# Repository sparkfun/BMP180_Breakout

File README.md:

**NOTE:** *This product has been retired from our catalog. If you are looking for more up-to-date info, please check out some of these resources to see how other users are still hacking and improving on this product.*
* *[SparkFun Forum](https://forum.sparkfun.com/)*
* *[Comments Here on GitHub](https://github.com/sparkfun/BMP180_Breakout_Arduino_Library/issues)*
* *[IRC Channel](https://www.sparkfun.com/news/263)*

BMP180_Breakout
===============

Breakout board and example code for the Bosch BMP180 barometric pressure sensor.

Product page: [www.sparkfun.com/products/11824](https://www.sparkfun.com/products/11824)

Datasheet: [github.com/sparkfun/BMP180_Breakout/blob/master/BMP180 Datasheet V2.5.pdf](https://github.com/sparkfun/BMP180_Breakout/blob/master/BMP180%20Datasheet%20V2.5.pdf?raw=true)

Github repository: [github.com/sparkfun/BMP180_Breakout](https://github.com/sparkfun/BMP180_Breakout)

Arduino library installation:
-------------------

This archive contains an Arduino library and example sketch showing how to use this sensor. The library must be installed onto your computer in order for the example code to work correctly.

If you haven't, install the free Arduino IDE (Integrated Development Environment), available at [www.arduino.cc](http://www.arduino.cc). This code was written using Arduino version 1.0.5. and updated to be used with the Arduino library manager of version 1.6.3.

To install without the manager, download the Arduino folder then use the Arduino IDE to add it.  From the IDE, go Sketch->Include Library->"Add .ZIP Library", then choose the Arduino folder that was downloaded.  The IDE will pick proper names from the library.properties file and put the libraries in your user sketch folder.

Teensy library installation:
-------------------

[A. Faruk](https://github.com/unalfaruk) was kind enough to create a version of this library for the [Teensy](https://www.pjrc.com/teensy/) microcontroller family. You can find information on installation and use of this library at: https://github.com/sparkfun/BMP180_Breakout/tree/master/Libraries/Teensy

Running the example sketch:
-------------------

<ol start=1>
<li>Connect the BMP180 breakout board to your Arduino. You can solder wires, use jumper wires and headers, etc.
<p>
"-" (GND) to GND
<br>
"+" (VDD) to 3.3V
<p>
(WARNING: do not connect "+" to 5V or the sensor will be damaged!)
<p>
You will also need to connect the I2C pins (SCL and SDA) to your Arduino.
These pins are different on different Arduino models:
<p>
<table>
<tr>
<td>Any Arduino</td>
<td>SDA&nbsp;</td>
<td>SCL</td>
</tr>
<tr>
<td>Uno, Redboard, Pro/Mini&nbsp;</td>
<td>A4</td>
<td>A5</td>
</tr>
<tr>
<td>Mega2560, Due</td>
<td>20</td>
<td>21</td>
</tr>
<tr>
<td>Leonardo, Pro/Micro</td>
<td>2</td>
<td>3</td>
</tr>
</table>
<p>
Leave the IO (VDDIO) pin unconnected. This pin is for connecting
the BMP180 to systems with lower logic levels such as 1.8V.
</li>
<li>
Connect your Arduino to your computer.
<p>
</li>
<li>
Start the Arduino IDE. Select the proper COM port and board type.
<p>
</li>
<li>
In the Arduino IDE, go to the File menu, and down to Examples/SFE_BMP180/SFE_BMP180_example. If you do not see this item, you likely did not install the library properly. See above.
<p>
</li>
<li>
Upload the sketch to your Arduino.
<p>
</li>
<li>
Open the Serial Monitor window (magnifying glass icon un upper right of IDE).
<p>
</li>
<li>
Set the Serial Monitor to 9600 baud (menu in bottom right).
<p>
</li>
</ol>
You should now be seeing pressure measurements in the Serial Monitor window. If you see errors, you may not have connected the BMP180 Breakout Board to your Arduino properly. See step 1 above.

If you have questions, don't hesistate to contact us at techsupport@sparkfun.com.

Have fun!
Your friends at SparkFun.

License Informatiom
-------------------

Software and hardware license information can be found at: https://github.com/sparkfun/BMP180_Breakout/blob/master/LICENSE.md

Authors
-------

 * Mike Grusin, SparkFun Electronics

Acknowledgements
----------------

 * The SFE_BMP180 library uses [floating-point equations](http://wmrx00.sourceforge.net/Arduino/BMP085-Calcs.pdf) for the BMP085 developed by the [Weather Station Data Logger project](http://wmrx00.sourceforge.net/).

  * Thank you to [A. Faruk](https://github.com/unalfaruk) for modifications to support the PJRC Teensy microcontroller family.

  * Thank you to [Asafe Silva](https://github.com/AsafeSilva) for providing support for alternate I2C implementations.

Changelog
---------
+ Release [V_1.1.0](https://github.com/sparkfun/BMP180_Breakout/tree/V_1.1.0)
	* Restructred for arduino IDE
	* Pulled in library

+ hardware V10 (release)

	* Minor updates
	* Library fork from SFE_BMP085

+ hardware V02 (proto)

	* Rearranged header: put VDD/GND/SDA/SCL in "standard" order
	* I2C pullups to VDDIO

+ hardware V01 (review)

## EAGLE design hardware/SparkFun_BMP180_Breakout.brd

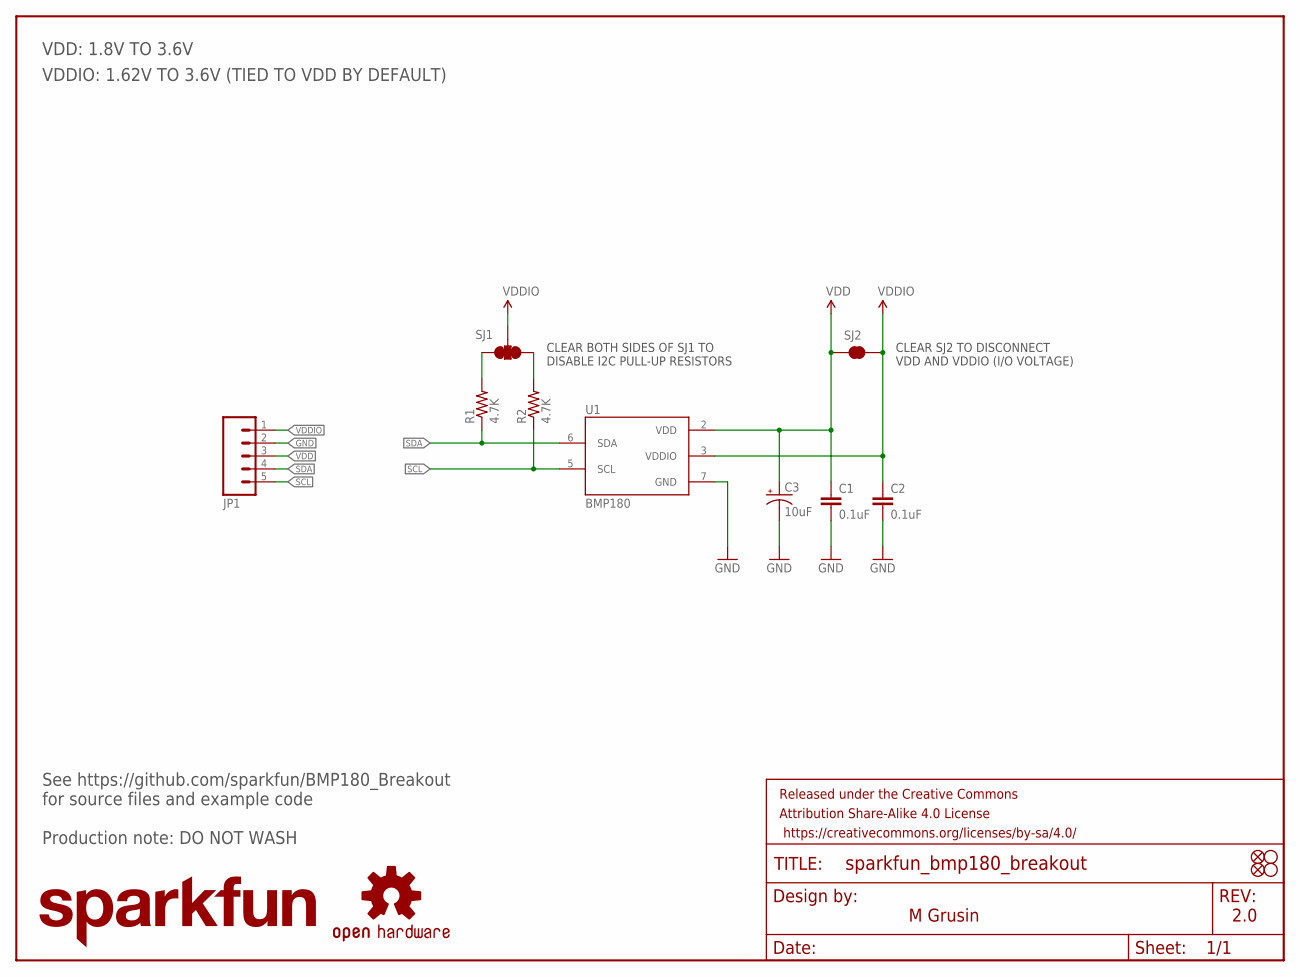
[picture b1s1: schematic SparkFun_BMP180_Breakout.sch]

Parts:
C1, C2: 0.1uF; 0603-CAP
C3: 10uF; EIA3216
FID1, FID2: FIDUCIALUFIDUCIAL; MICRO-FIDUCIAL
FRAME1: FRAME-LETTER; CREATIVE_COMMONS
JP1: M05_ROUNDONLY_NOSILK; 1X05_ROUNDONLY_NOSILK
LOGO2: OSHW-LOGOS; OSHW-LOGO-S
LOGO3: SFE_LOGO_NAME.1_INCH; SFE_LOGO_NAME_.1
R1, R2: 4.7K; 0603-RES
SJ1: SOLDERJUMPER_2WAYPASTE1&2&3; SJ_3_PASTE1&2&3
SJ2: SOLDERJUMPERNC; SJ_2S
STANDOFF1, STANDOFF2: STAND-OFF
U1: BMP180

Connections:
GND: C1.2, C2.2, C3.C (-), JP1.2, U1.7 (GND)
unnamed: R1.2, SJ1.3
unnamed: R2.2, SJ1.1
SCL: JP1.5, R2.1, U1.5 (SCL)
SDA: JP1.4, R1.1, U1.6 (SDA)
VDD: C1.1, C3.A (+), JP1.3, SJ2.1, U1.2 (VDD)
VDDIO: C2.1, JP1.1, SJ1.2, SJ2.2, U1.3 (VDDIO)

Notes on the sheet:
M Grusin
CLEAR BOTH SIDES OF SJ1 TO DISABLE I2C PULL-UP RESISTORS
CLEAR SJ2 TO DISCONNECT VDD AND VDDIO (I/O VOLTAGE)
2.0
Production note: DO NOT WASH
See https://github.com/sparkfun/BMP180_Breakout for source files and example code
VDD: 1.8V TO 3.6V
VDDIO: 1.62V TO 3.6V (TIED TO VDD BY DEFAULT)

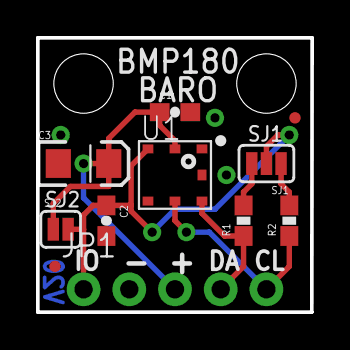
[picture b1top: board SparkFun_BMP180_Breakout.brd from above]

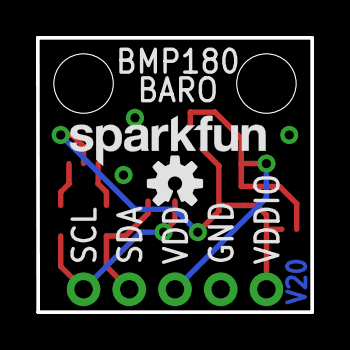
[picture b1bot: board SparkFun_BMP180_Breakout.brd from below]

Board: 2 copper layers, 15.2 x 15.2 mm, 16 parts (2 on the bottom side), 7 nets.

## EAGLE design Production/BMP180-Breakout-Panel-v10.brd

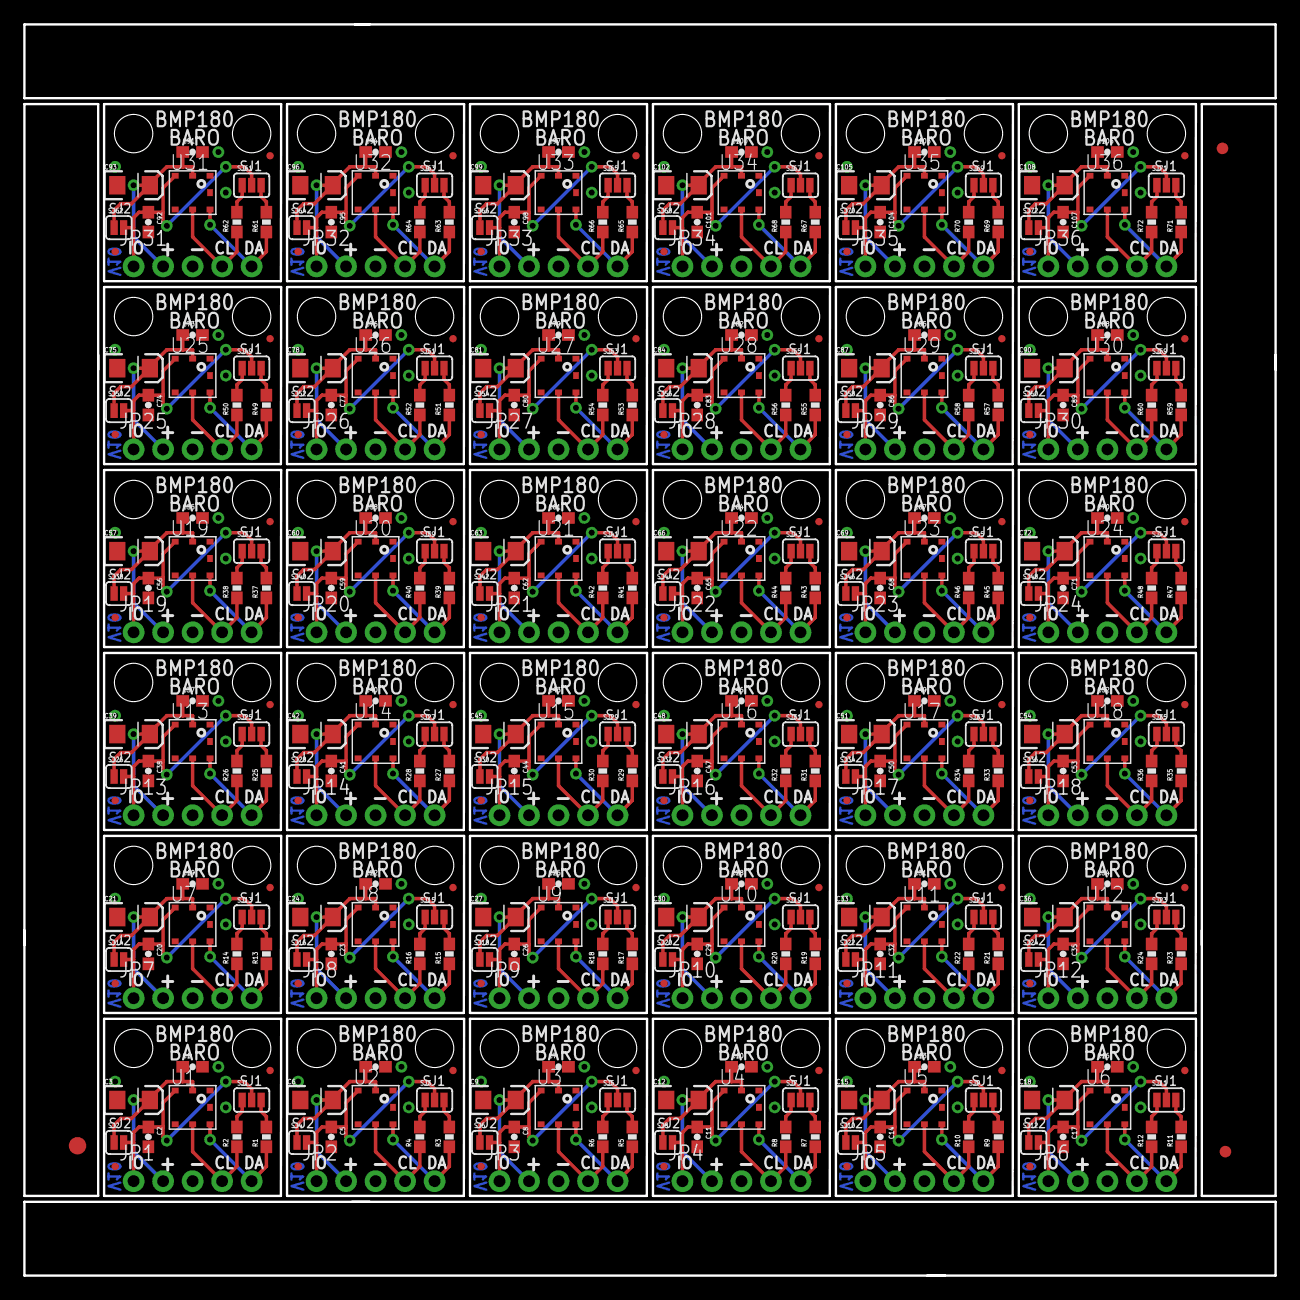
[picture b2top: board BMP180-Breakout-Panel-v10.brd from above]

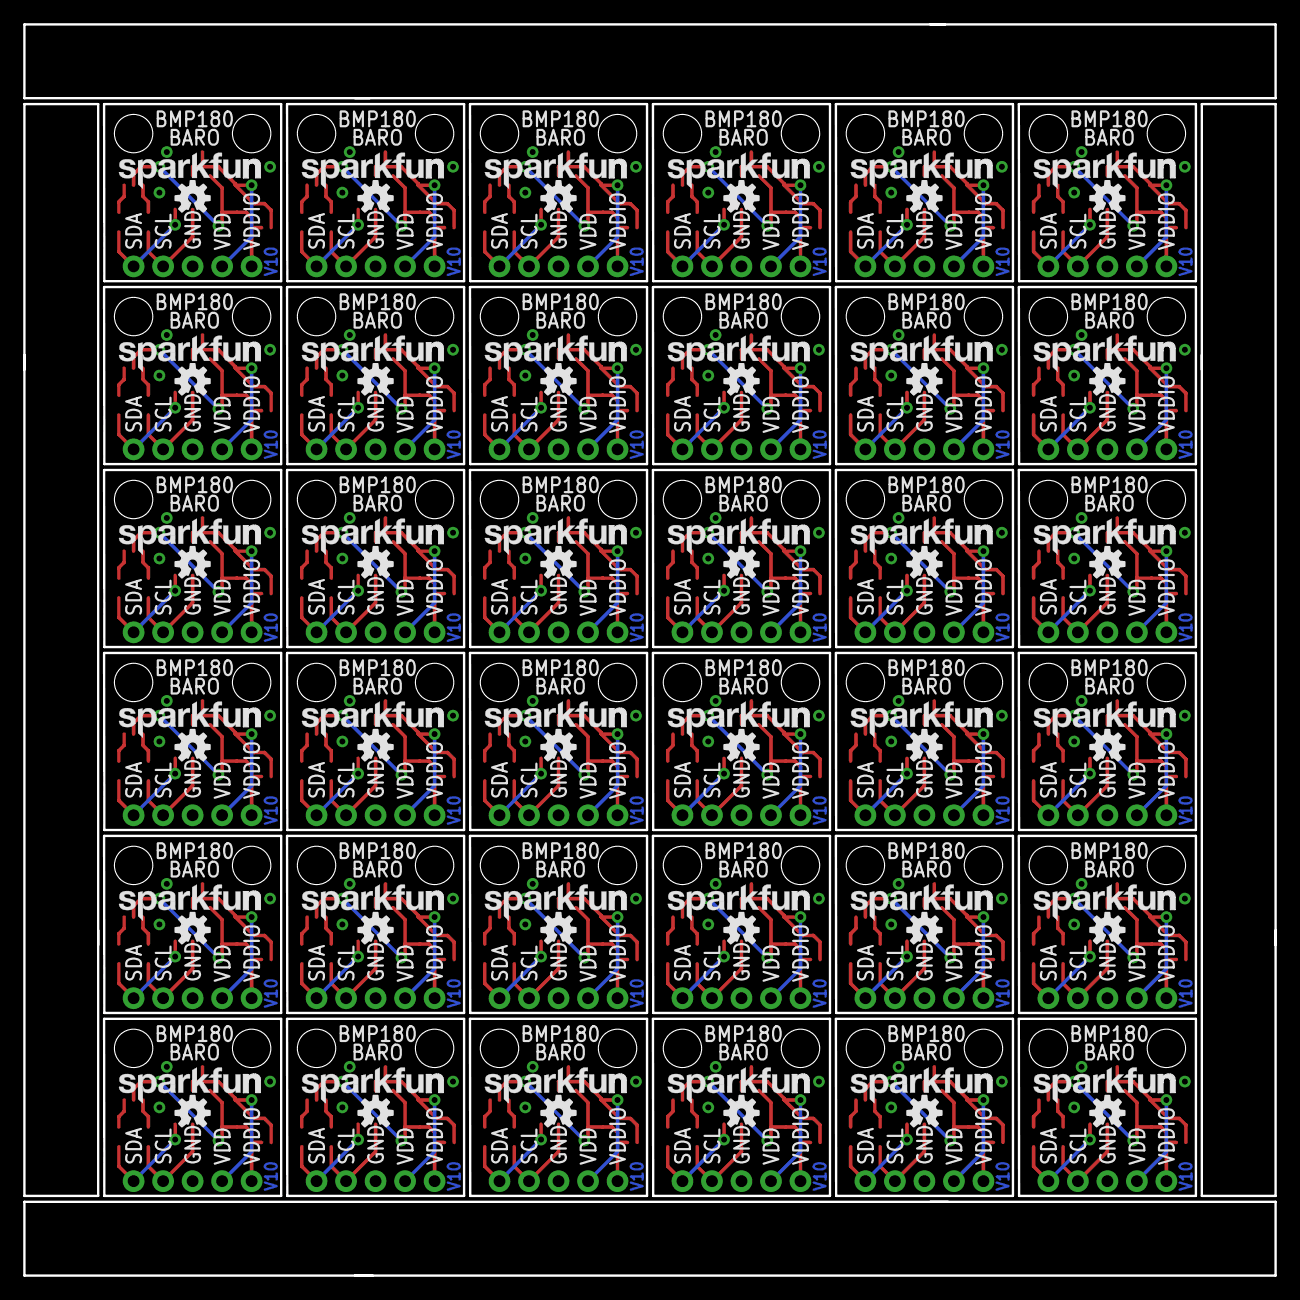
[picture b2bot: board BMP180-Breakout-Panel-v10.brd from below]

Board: 2 copper layers, 107.7 x 107.7 mm, 543 parts (72 on the bottom side), 252 nets.

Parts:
C1, C2, C4, C5, C7, C8, C10, C11, C13, C14, C16, C17, C19, C20, C22, C23, C25, C26, C28, C29, C31, C32, C34, C35, C37, C38, C40, C41, C43, C44, C46, C47, C49, C50, C52, C53, C55, C56, C58, C59, C61, C62, C64, C65, C67, C68, C70, C71, C73, C74, C76, C77, C79, C80, C82, C83, C85, C86, C88, C89, C91, C92, C94, C95, C97, C98, C100, C101, C103, C104, C106, C107: 0.1uF; 0603-CAP
C3, C6, C9, C12, C15, C18, C21, C24, C27, C30, C33, C36, C39, C42, C45, C48, C51, C54, C57, C60, C63, C66, C69, C72, C75, C78, C81, C84, C87, C90, C93, C96, C99, C102, C105, C108: 10uF; EIA3216
E$1: FIDUCIAL-1.5X3
E$4, E$8: FIDUCIAL-1X2
FID1, FID2, FID3, FID4, FID5, FID6, FID7, FID8, FID9, FID10, FID11, FID12, FID13, FID14, FID15, FID16, FID17, FID18, FID19, FID20, FID21, FID22, FID23, FID24, FID25, FID26, FID27, FID28, FID29, FID30, FID31, FID32, FID33, FID34, FID35, FID36, FID37, FID38, FID39, FID40, FID41, FID42, FID43, FID44, FID45, FID46, FID47, FID48, FID49, FID50, FID51, FID52, FID53, FID54, FID55, FID56, FID57, FID58, FID59, FID60, FID61, FID62, FID63, FID64, FID65, FID66, FID67, FID68, FID69, FID70, FID71, FID72: FIDUCIALUFIDUCIAL; MICRO-FIDUCIAL
JP1, JP2, JP3, JP4, JP5, JP6, JP7, JP8, JP9, JP10, JP11, JP12, JP13, JP14, JP15, JP16, JP17, JP18, JP19, JP20, JP21, JP22, JP23, JP24, JP25, JP26, JP27, JP28, JP29, JP30, JP31, JP32, JP33, JP34, JP35, JP36: 1X05_ROUNDONLY_NOSILK
LOGO1, LOGO3, LOGO5, LOGO7, LOGO9, LOGO11, LOGO13, LOGO15, LOGO17, LOGO19, LOGO21, LOGO23, LOGO25, LOGO27, LOGO29, LOGO31, LOGO33, LOGO35, LOGO37, LOGO39, LOGO41, LOGO43, LOGO45, LOGO47, LOGO49, LOGO51, LOGO53, LOGO55, LOGO57, LOGO59, LOGO61, LOGO63, LOGO65, LOGO67, LOGO69, LOGO71: LOGO-SFENW2; SFE-NEW-WEB
LOGO2, LOGO4, LOGO6, LOGO8, LOGO10, LOGO12, LOGO14, LOGO16, LOGO18, LOGO20, LOGO22, LOGO24, LOGO26, LOGO28, LOGO30, LOGO32, LOGO34, LOGO36, LOGO38, LOGO40, LOGO42, LOGO44, LOGO46, LOGO48, LOGO50, LOGO52, LOGO54, LOGO56, LOGO58, LOGO60, LOGO62, LOGO64, LOGO66, LOGO68, LOGO70, LOGO72: OSHW-LOGOS; OSHW-LOGO-S
R1, R2, R3, R4, R5, R6, R7, R8, R9, R10, R11, R12, R13, R14, R15, R16, R17, R18, R19, R20, R21, R22, R23, R24, R25, R26, R27, R28, R29, R30, R31, R32, R33, R34, R35, R36, R37, R38, R39, R40, R41, R42, R43, R44, R45, R46, R47, R48, R49, R50, R51, R52, R53, R54, R55, R56, R57, R58, R59, R60, R61, R62, R63, R64, R65, R66, R67, R68, R69, R70, R71, R72: 4.7K; 0603-RES
SJ1, SJ3, SJ5, SJ7, SJ9, SJ11, SJ13, SJ15, SJ17, SJ19, SJ21, SJ23, SJ25, SJ27, SJ29, SJ31, SJ33, SJ35, SJ37, SJ39, SJ41, SJ43, SJ45, SJ47, SJ49, SJ51, SJ53, SJ55, SJ57, SJ59, SJ61, SJ63, SJ65, SJ67, SJ69, SJ71: SJ_3_PASTE1&2&3
SJ2, SJ4, SJ6, SJ8, SJ10, SJ12, SJ14, SJ16, SJ18, SJ20, SJ22, SJ24, SJ26, SJ28, SJ30, SJ32, SJ34, SJ36, SJ38, SJ40, SJ42, SJ44, SJ46, SJ48, SJ50, SJ52, SJ54, SJ56, SJ58, SJ60, SJ62, SJ64, SJ66, SJ68, SJ70, SJ72: SJ_2S
STANDOFF1, STANDOFF2, STANDOFF3, STANDOFF4, STANDOFF5, STANDOFF6, STANDOFF7, STANDOFF8, STANDOFF9, STANDOFF10, STANDOFF11, STANDOFF12, STANDOFF13, STANDOFF14, STANDOFF15, STANDOFF16, STANDOFF17, STANDOFF18, STANDOFF19, STANDOFF20, STANDOFF21, STANDOFF22, STANDOFF23, STANDOFF24, STANDOFF25, STANDOFF26, STANDOFF27, STANDOFF28, STANDOFF29, STANDOFF30, STANDOFF31, STANDOFF32, STANDOFF33, STANDOFF34, STANDOFF35, STANDOFF36, STANDOFF37, STANDOFF38, STANDOFF39, STANDOFF40, STANDOFF41, STANDOFF42, STANDOFF43, STANDOFF44, STANDOFF45, STANDOFF46, STANDOFF47, STANDOFF48, STANDOFF49, STANDOFF50, STANDOFF51, STANDOFF52, STANDOFF53, STANDOFF54, STANDOFF55, STANDOFF56, STANDOFF57, STANDOFF58, STANDOFF59, STANDOFF60, STANDOFF61, STANDOFF62, STANDOFF63, STANDOFF64, STANDOFF65, STANDOFF66, STANDOFF67, STANDOFF68, STANDOFF69, STANDOFF70, STANDOFF71, STANDOFF72: STAND-OFF
U1, U2, U3, U4, U5, U6, U7, U8, U9, U10, U11, U12, U13, U14, U15, U16, U17, U18, U19, U20, U21, U22, U23, U24, U25, U26, U27, U28, U29, U30, U31, U32, U33, U34, U35, U36: BMP180

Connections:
GND: C1.2, C2.2, C3.C, JP1.3, U1.7
GND1: C4.2, C5.2, C6.C, JP2.3, U2.7
GND2: C7.2, C8.2, C9.C, JP3.3, U3.7
GND3: C10.2, C11.2, C12.C, JP4.3, U4.7
GND4: C13.2, C14.2, C15.C, JP5.3, U5.7
GND5: C16.2, C17.2, C18.C, JP6.3, U6.7
GND6: C19.2, C20.2, C21.C, JP7.3, U7.7
GND7: C22.2, C23.2, C24.C, JP8.3, U8.7
GND8: C25.2, C26.2, C27.C, JP9.3, U9.7
GND9: C28.2, C29.2, C30.C, JP10.3, U10.7
GND10: C31.2, C32.2, C33.C, JP11.3, U11.7
GND11: C34.2, C35.2, C36.C, JP12.3, U12.7
GND12: C37.2, C38.2, C39.C, JP13.3, U13.7
GND13: C40.2, C41.2, C42.C, JP14.3, U14.7
GND14: C43.2, C44.2, C45.C, JP15.3, U15.7
GND15: C46.2, C47.2, C48.C, JP16.3, U16.7
GND16: C49.2, C50.2, C51.C, JP17.3, U17.7
GND17: C52.2, C53.2, C54.C, JP18.3, U18.7
GND18: C55.2, C56.2, C57.C, JP19.3, U19.7
GND19: C58.2, C59.2, C60.C, JP20.3, U20.7
GND20: C61.2, C62.2, C63.C, JP21.3, U21.7
GND21: C64.2, C65.2, C66.C, JP22.3, U22.7
GND22: C67.2, C68.2, C69.C, JP23.3, U23.7
GND23: C70.2, C71.2, C72.C, JP24.3, U24.7
GND24: C73.2, C74.2, C75.C, JP25.3, U25.7
GND25: C76.2, C77.2, C78.C, JP26.3, U26.7
GND26: C79.2, C80.2, C81.C, JP27.3, U27.7
GND27: C82.2, C83.2, C84.C, JP28.3, U28.7
GND28: C85.2, C86.2, C87.C, JP29.3, U29.7
GND29: C88.2, C89.2, C90.C, JP30.3, U30.7
GND30: C91.2, C92.2, C93.C, JP31.3, U31.7
GND31: C94.2, C95.2, C96.C, JP32.3, U32.7
GND32: C97.2, C98.2, C99.C, JP33.3, U33.7
GND33: C100.2, C101.2, C102.C, JP34.3, U34.7
GND34: C103.2, C104.2, C105.C, JP35.3, U35.7
GND35: C106.2, C107.2, C108.C, JP36.3, U36.7
unnamed: R1.2, SJ1.3
unnamed: R2.2, SJ1.1
unnamed: R3.2, SJ3.3
unnamed: R4.2, SJ3.1
unnamed: R5.2, SJ5.3
unnamed: R6.2, SJ5.1
unnamed: R7.2, SJ7.3
unnamed: R8.2, SJ7.1
unnamed: R9.2, SJ9.3
unnamed: R10.2, SJ9.1
unnamed: R11.2, SJ11.3
unnamed: R12.2, SJ11.1
unnamed: R13.2, SJ13.3
unnamed: R14.2, SJ13.1
unnamed: R15.2, SJ15.3
unnamed: R16.2, SJ15.1
unnamed: R17.2, SJ17.3
unnamed: R18.2, SJ17.1
unnamed: R19.2, SJ19.3
unnamed: R20.2, SJ19.1
unnamed: R21.2, SJ21.3
unnamed: R22.2, SJ21.1
unnamed: R23.2, SJ23.3
unnamed: R24.2, SJ23.1
unnamed: R25.2, SJ25.3
unnamed: R26.2, SJ25.1
unnamed: R27.2, SJ27.3
unnamed: R28.2, SJ27.1
unnamed: R29.2, SJ29.3
unnamed: R30.2, SJ29.1
unnamed: R31.2, SJ31.3
unnamed: R32.2, SJ31.1
unnamed: R33.2, SJ33.3
unnamed: R34.2, SJ33.1
unnamed: R35.2, SJ35.3
unnamed: R36.2, SJ35.1
unnamed: R37.2, SJ37.3
unnamed: R38.2, SJ37.1
unnamed: R39.2, SJ39.3
unnamed: R40.2, SJ39.1
unnamed: R41.2, SJ41.3
unnamed: R42.2, SJ41.1
unnamed: R43.2, SJ43.3
unnamed: R44.2, SJ43.1
unnamed: R45.2, SJ45.3
unnamed: R46.2, SJ45.1
unnamed: R47.2, SJ47.3
unnamed: R48.2, SJ47.1
unnamed: R49.2, SJ49.3
unnamed: R50.2, SJ49.1
unnamed: R51.2, SJ51.3
unnamed: R52.2, SJ51.1
unnamed: R53.2, SJ53.3
unnamed: R54.2, SJ53.1
unnamed: R55.2, SJ55.3
unnamed: R56.2, SJ55.1
unnamed: R57.2, SJ57.3
unnamed: R58.2, SJ57.1
unnamed: R59.2, SJ59.3
unnamed: R60.2, SJ59.1
unnamed: R61.2, SJ61.3
unnamed: R62.2, SJ61.1
unnamed: R63.2, SJ63.3
unnamed: R64.2, SJ63.1
unnamed: R65.2, SJ65.3
unnamed: R66.2, SJ65.1
unnamed: R67.2, SJ67.3
unnamed: R68.2, SJ67.1
unnamed: R69.2, SJ69.3
unnamed: R70.2, SJ69.1
unnamed: R71.2, SJ71.3
unnamed: R72.2, SJ71.1
SCL: JP1.4, R2.1, U1.5
SCL1: JP2.4, R4.1, U2.5
SCL2: JP3.4, R6.1, U3.5
SCL3: JP4.4, R8.1, U4.5
SCL4: JP5.4, R10.1, U5.5
SCL5: JP6.4, R12.1, U6.5
SCL6: JP7.4, R14.1, U7.5
SCL7: JP8.4, R16.1, U8.5
SCL8: JP9.4, R18.1, U9.5
SCL9: JP10.4, R20.1, U10.5
SCL10: JP11.4, R22.1, U11.5
SCL11: JP12.4, R24.1, U12.5
SCL12: JP13.4, R26.1, U13.5
SCL13: JP14.4, R28.1, U14.5
SCL14: JP15.4, R30.1, U15.5
SCL15: JP16.4, R32.1, U16.5
SCL16: JP17.4, R34.1, U17.5
SCL17: JP18.4, R36.1, U18.5
SCL18: JP19.4, R38.1, U19.5
SCL19: JP20.4, R40.1, U20.5
SCL20: JP21.4, R42.1, U21.5
SCL21: JP22.4, R44.1, U22.5
SCL22: JP23.4, R46.1, U23.5
SCL23: JP24.4, R48.1, U24.5
SCL24: JP25.4, R50.1, U25.5
SCL25: JP26.4, R52.1, U26.5
SCL26: JP27.4, R54.1, U27.5
SCL27: JP28.4, R56.1, U28.5
SCL28: JP29.4, R58.1, U29.5
SCL29: JP30.4, R60.1, U30.5
SCL30: JP31.4, R62.1, U31.5
SCL31: JP32.4, R64.1, U32.5
SCL32: JP33.4, R66.1, U33.5
SCL33: JP34.4, R68.1, U34.5
SCL34: JP35.4, R70.1, U35.5
SCL35: JP36.4, R72.1, U36.5
SDA: JP1.5, R1.1, U1.6
SDA1: JP2.5, R3.1, U2.6
SDA2: JP3.5, R5.1, U3.6
SDA3: JP4.5, R7.1, U4.6
SDA4: JP5.5, R9.1, U5.6
SDA5: JP6.5, R11.1, U6.6
SDA6: JP7.5, R13.1, U7.6
SDA7: JP8.5, R15.1, U8.6
SDA8: JP9.5, R17.1, U9.6
SDA9: JP10.5, R19.1, U10.6
SDA10: JP11.5, R21.1, U11.6
SDA11: JP12.5, R23.1, U12.6
SDA12: JP13.5, R25.1, U13.6
SDA13: JP14.5, R27.1, U14.6
SDA14: JP15.5, R29.1, U15.6
SDA15: JP16.5, R31.1, U16.6
SDA16: JP17.5, R33.1, U17.6
SDA17: JP18.5, R35.1, U18.6
SDA18: JP19.5, R37.1, U19.6
SDA19: JP20.5, R39.1, U20.6
SDA20: JP21.5, R41.1, U21.6
SDA21: JP22.5, R43.1, U22.6
SDA22: JP23.5, R45.1, U23.6
SDA23: JP24.5, R47.1, U24.6
SDA24: JP25.5, R49.1, U25.6
SDA25: JP26.5, R51.1, U26.6
SDA26: JP27.5, R53.1, U27.6
SDA27: JP28.5, R55.1, U28.6
SDA28: JP29.5, R57.1, U29.6
SDA29: JP30.5, R59.1, U30.6
SDA30: JP31.5, R61.1, U31.6
SDA31: JP32.5, R63.1, U32.6
SDA32: JP33.5, R65.1, U33.6
SDA33: JP34.5, R67.1, U34.6
SDA34: JP35.5, R69.1, U35.6
SDA35: JP36.5, R71.1, U36.6
VDD: C1.1, C3.A, JP1.2, SJ2.1, U1.2
VDD1: C4.1, C6.A, JP2.2, SJ4.1, U2.2
VDD2: C7.1, C9.A, JP3.2, SJ6.1, U3.2
VDD3: C10.1, C12.A, JP4.2, SJ8.1, U4.2
VDD4: C13.1, C15.A, JP5.2, SJ10.1, U5.2
VDD5: C16.1, C18.A, JP6.2, SJ12.1, U6.2
VDD6: C19.1, C21.A, JP7.2, SJ14.1, U7.2
VDD7: C22.1, C24.A, JP8.2, SJ16.1, U8.2
VDD8: C25.1, C27.A, JP9.2, SJ18.1, U9.2
VDD9: C28.1, C30.A, JP10.2, SJ20.1, U10.2
VDD10: C31.1, C33.A, JP11.2, SJ22.1, U11.2
VDD11: C34.1, C36.A, JP12.2, SJ24.1, U12.2
VDD12: C37.1, C39.A, JP13.2, SJ26.1, U13.2
VDD13: C40.1, C42.A, JP14.2, SJ28.1, U14.2
VDD14: C43.1, C45.A, JP15.2, SJ30.1, U15.2
VDD15: C46.1, C48.A, JP16.2, SJ32.1, U16.2
VDD16: C49.1, C51.A, JP17.2, SJ34.1, U17.2
VDD17: C52.1, C54.A, JP18.2, SJ36.1, U18.2
VDD18: C55.1, C57.A, JP19.2, SJ38.1, U19.2
VDD19: C58.1, C60.A, JP20.2, SJ40.1, U20.2
VDD20: C61.1, C63.A, JP21.2, SJ42.1, U21.2
VDD21: C64.1, C66.A, JP22.2, SJ44.1, U22.2
VDD22: C67.1, C69.A, JP23.2, SJ46.1, U23.2
VDD23: C70.1, C72.A, JP24.2, SJ48.1, U24.2
VDD24: C73.1, C75.A, JP25.2, SJ50.1, U25.2
VDD25: C76.1, C78.A, JP26.2, SJ52.1, U26.2
VDD26: C79.1, C81.A, JP27.2, SJ54.1, U27.2
VDD27: C82.1, C84.A, JP28.2, SJ56.1, U28.2
VDD28: C85.1, C87.A, JP29.2, SJ58.1, U29.2
VDD29: C88.1, C90.A, JP30.2, SJ60.1, U30.2
VDD30: C91.1, C93.A, JP31.2, SJ62.1, U31.2
VDD31: C94.1, C96.A, JP32.2, SJ64.1, U32.2
VDD32: C97.1, C99.A, JP33.2, SJ66.1, U33.2
VDD33: C100.1, C102.A, JP34.2, SJ68.1, U34.2
VDD34: C103.1, C105.A, JP35.2, SJ70.1, U35.2
VDD35: C106.1, C108.A, JP36.2, SJ72.1, U36.2
VDDIO: C2.1, JP1.1, SJ1.2, SJ2.2, U1.3
VDDIO1: C5.1, JP2.1, SJ3.2, SJ4.2, U2.3
VDDIO2: C8.1, JP3.1, SJ5.2, SJ6.2, U3.3
VDDIO3: C11.1, JP4.1, SJ7.2, SJ8.2, U4.3
VDDIO4: C14.1, JP5.1, SJ9.2, SJ10.2, U5.3
VDDIO5: C17.1, JP6.1, SJ11.2, SJ12.2, U6.3
VDDIO6: C20.1, JP7.1, SJ13.2, SJ14.2, U7.3
VDDIO7: C23.1, JP8.1, SJ15.2, SJ16.2, U8.3
VDDIO8: C26.1, JP9.1, SJ17.2, SJ18.2, U9.3
VDDIO9: C29.1, JP10.1, SJ19.2, SJ20.2, U10.3
VDDIO10: C32.1, JP11.1, SJ21.2, SJ22.2, U11.3
VDDIO11: C35.1, JP12.1, SJ23.2, SJ24.2, U12.3
VDDIO12: C38.1, JP13.1, SJ25.2, SJ26.2, U13.3
VDDIO13: C41.1, JP14.1, SJ27.2, SJ28.2, U14.3
VDDIO14: C44.1, JP15.1, SJ29.2, SJ30.2, U15.3
VDDIO15: C47.1, JP16.1, SJ31.2, SJ32.2, U16.3
VDDIO16: C50.1, JP17.1, SJ33.2, SJ34.2, U17.3
VDDIO17: C53.1, JP18.1, SJ35.2, SJ36.2, U18.3
VDDIO18: C56.1, JP19.1, SJ37.2, SJ38.2, U19.3
VDDIO19: C59.1, JP20.1, SJ39.2, SJ40.2, U20.3
VDDIO20: C62.1, JP21.1, SJ41.2, SJ42.2, U21.3
VDDIO21: C65.1, JP22.1, SJ43.2, SJ44.2, U22.3
VDDIO22: C68.1, JP23.1, SJ45.2, SJ46.2, U23.3
VDDIO23: C71.1, JP24.1, SJ47.2, SJ48.2, U24.3
VDDIO24: C74.1, JP25.1, SJ49.2, SJ50.2, U25.3
VDDIO25: C77.1, JP26.1, SJ51.2, SJ52.2, U26.3
VDDIO26: C80.1, JP27.1, SJ53.2, SJ54.2, U27.3
VDDIO27: C83.1, JP28.1, SJ55.2, SJ56.2, U28.3
VDDIO28: C86.1, JP29.1, SJ57.2, SJ58.2, U29.3
VDDIO29: C89.1, JP30.1, SJ59.2, SJ60.2, U30.3
VDDIO30: C92.1, JP31.1, SJ61.2, SJ62.2, U31.3
VDDIO31: C95.1, JP32.1, SJ63.2, SJ64.2, U32.3
VDDIO32: C98.1, JP33.1, SJ65.2, SJ66.2, U33.3
VDDIO33: C101.1, JP34.1, SJ67.2, SJ68.2, U34.3
VDDIO34: C104.1, JP35.1, SJ69.2, SJ70.2, U35.3
VDDIO35: C107.1, JP36.1, SJ71.2, SJ72.2, U36.3

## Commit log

2013-04-16 minor readme edit
2013-04-16 minor changes to eagle files re. group review
2013-04-16 final proto hardware, initial library
    Library copied and renamed from BMP085 floating-point library (see USB
    Weather Board)
2013-09-20 Library in progress
2013-10-25 Review for reds
    Minor updates to PCB, updated library and example code, added datasheet
    and readme
2013-10-25 Added an altimeter example
2013-10-28 Minor changes for reds (V10)
    Added silk to solder jumpers
    Added BMP180 part to SparkFun Eagle Libraries
2013-10-30 Added microfiducials
2013-10-30 Created Panel
2013-11-11 Minor library edits for code review
2013-11-13 Renamed datasheet
2014-01-04 library and example cleanup
2014-01-09 Moar readme edits
2014-01-09 Final example updates for release
2015-03-04 Changing 16 bit Arduino integers to uint16_t to make it compatible with 32b Teensy integers (and possibly Arduino Due's)
2015-04-26 fixed link
2015-04-26 Squashed 'Libraries/Arduino/' content from commit ee6ef49
    git-subtree-dir: Libraries/Arduino
    git-subtree-split: ee6ef491cf48a35091de4cd5d86c529a7980a9df
2015-04-26 Updating to new library structure
2015-04-29 fixed library.properties
2015-04-29 pulled lib
2015-04-29 Squashed 'Libraries/Arduino/' content from commit 2ba6578
    git-subtree-dir: Libraries/Arduino
    git-subtree-split: 2ba6578635be3bbba9798e9826d1f68f2fc34cd3
2015-04-29 fixed version number
2015-06-02 Patching ints, cleaning up library files
2015-06-02 Updating repo files, moving datasheet to documentation directory
2015-07-09 Version 2.0, initial commit
    Rerouted connector for new standard I2C pinout.
    Cleaned up layout and schematic per standards.
2016-01-08 add combatibility for ESP8266
2016-01-08 remove old code
2016-11-12 Updates for quality
    Removed an unused variable that served no purpose.
    Changed a variable type from char to int that was being used only as an array index
    as my compiler doesn't like chars used as indices.
2017-11-22 Update SFE_BMP180.h
    Update to use other instances of the 'Wire.h' Library
2017-11-22 Update SFE_BMP180.cpp
    Update to use other instances of the Wire Library
2018-02-25 BMP180 Library for Teensy. v1
2018-02-25 Update README.md
    Info Teensyduino
2018-03-26 Updated readme and license
    Updated main readme and license files to acknowledge recent pull requests (thank you!)
2018-03-26 minor syntax
2018-04-14 Multiple interface feature is added. This library can be used with Teensy/Arduino devices that has multiple i2c interfaces.
2018-04-14 Info about of update was added.
2018-04-14 The sketch is rewritten to show new features.
2018-04-14 This source cod for users who want to work with i2c_t3 library.
2018-04-14 Info about of update were added.
2018-04-14 About new features.
2018-04-14 About the new feature

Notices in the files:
parts and their libraries:
SparkFun-Aesthetics: Licensing: CC v3.0 Share-Alike You are welcome to use this library for commercial purposes.
SparkFun-Aesthetics: Released under the Creative Commons Attribution Share-Alike 4.0 License
SparkFun-Aesthetics: https://creativecommons.org/licenses/by-sa/4.0
